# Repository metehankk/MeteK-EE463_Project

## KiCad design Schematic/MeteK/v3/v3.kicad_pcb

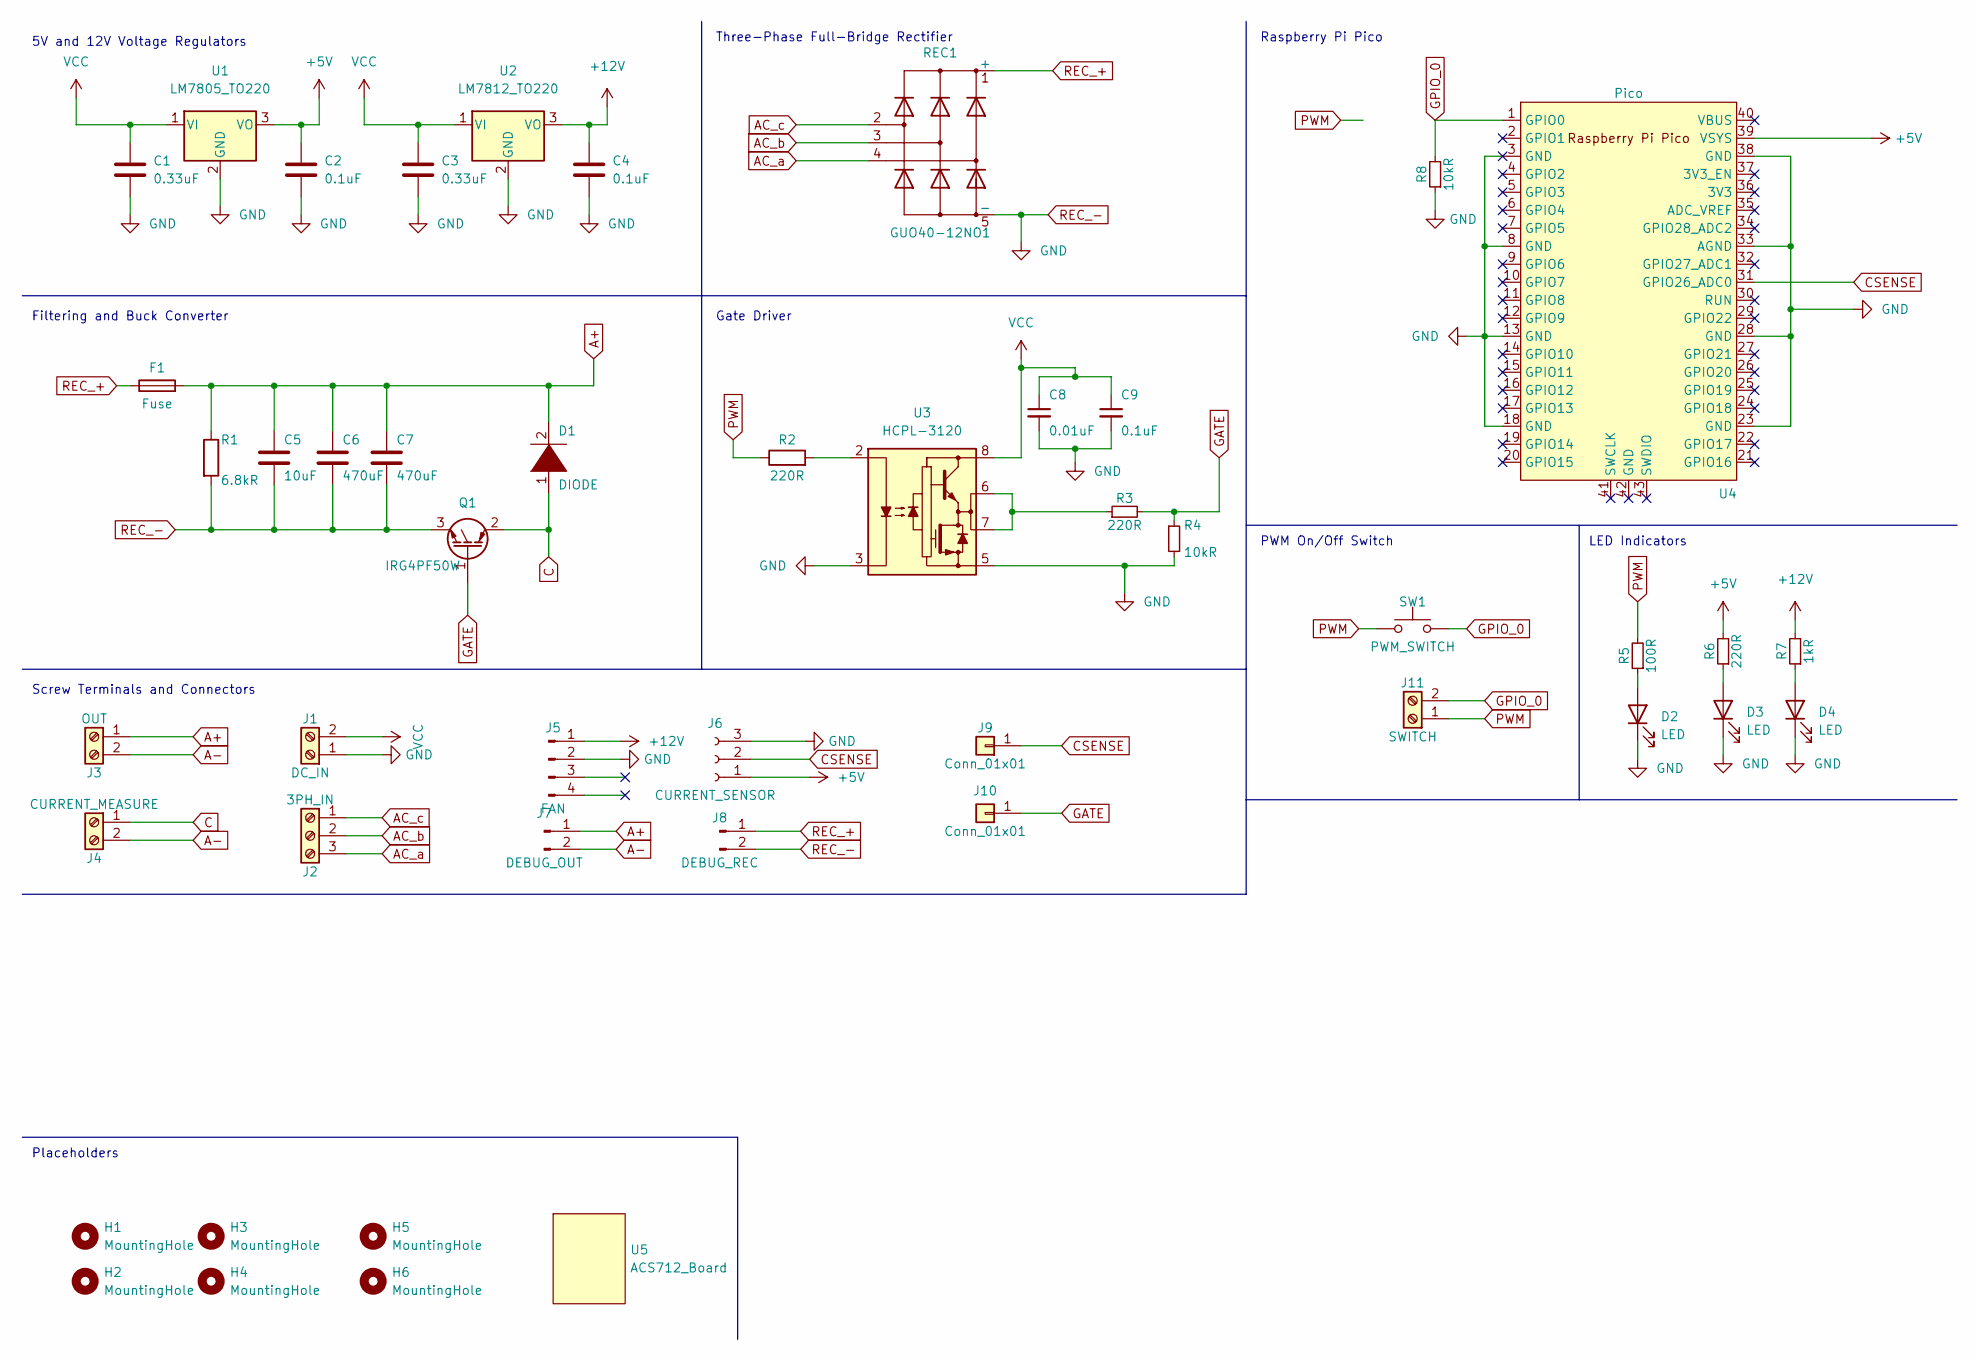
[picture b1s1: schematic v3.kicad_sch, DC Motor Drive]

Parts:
C1, C3: 0.33uF; C_1206_3216Metric_Pad1.33x1.80mm_HandSolder
C2, C4: 0.1uF; C_1206_3216Metric_Pad1.33x1.80mm_HandSolder
C5: 10uF; C_Rect_L29.0mm_W16.0mm_P27.50mm_MKT
C6, C7: 470uF; CP_Radial_D35.0mm_H50.0mm_P10.00mm_SnapIn
C8: 0.01uF; C_1206_3216Metric
C9: 0.1uF; C_1206_3216Metric
D1: DIODE; TO-220-2_Vertical
D2, D3, D4: LED; LED_D3.0mm
F1: Fuse; Fuseholder_Clip-5x20mm_Bel_FC-203-22_Lateral_P17.80x5.00mm_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
H1, H2, H3, H4: MountingHole; MountingHole_3.2mm_M3_Pad_Via
H5, H6: MountingHole; MountingHole_2.1mm
J1: DC_IN; TerminalBlock_Phoenix_MKDS-3-2-5.08_1x02_P5.08mm_Horizontal
J2: 3PH_IN; P7.62mm_ScrewTerminal_01x03
J3: OUT; P7.62mm_ScrewTerminal_01x02
J4: CURRENT_MEASURE; P7.62mm_ScrewTerminal_01x02
J5: FAN; PhoenixContact_MSTBVA_2,5_4-G-5,08_1x04_P5.08mm_Vertical
J6: CURRENT_SENSOR; PinSocket_1x03_P2.54mm_Vertical
J7: DEBUG_OUT; PinHeader_1x02_P2.54mm_Vertical
J8: DEBUG_REC; PinHeader_1x02_P2.54mm_Vertical
J9, J10: Conn_01x01; PinHeader_1x01_P2.54mm_Vertical
J11: SWITCH; TerminalBlock_Phoenix_MPT-0,5-2-2.54_1x02_P2.54mm_Horizontal
Q1: IRG4PF50W; TO-247-3_Vertical
R1: 6.8kR; R_Axial_Power_L50.0mm_W9.0mm_P55.88mm
R2, R3, R6: 220R; R_1206_3216Metric_Pad1.30x1.75mm_HandSolder
R4, R8: 10kR; R_1206_3216Metric_Pad1.30x1.75mm_HandSolder
R5: 100R; R_1206_3216Metric_Pad1.30x1.75mm_HandSolder
R7: 1kR; R_1206_3216Metric_Pad1.30x1.75mm_HandSolder
REC1: GUO40-12NO1; Diode_Bridge_IXYS_GUFP
SW1: PWM_SWITCH
U1: LM7805_TO220; TO-220-3_Vertical
U2: LM7812_TO220; TO-220-3_Vertical
U3: HCPL-3120; DIP-8_W7.62mm
U4: Pico; RPi_Pico_SMD_TH
U5: ACS712_Board; Current_sensor

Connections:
+5V: C2.1, J6.1, R6.2, U1.3 (VO), U4.39 (VSYS)
+12V: C4.1, J5.1, R7.2, U2.3 (VO)
A+: C5.1, C6.1, C7.1, D1.2 (A), F1.2, J3.1, J7.1, R1.1
A-: J3.2, J4.2, J7.2
AC_a: J2.3, REC1.4
AC_b: J2.2, REC1.3
AC_c: J2.1, REC1.2
C: D1.1 (K), J4.1, Q1.2 (C)
CSENSE: J6.2, J9.1, U4.31 (GPIO26_ADC0)
GATE: J10.1, Q1.1 (G), R3.2, R4.1
GPIO_0: J11.2, R8.2, SW1.2, U4.1 (GPIO0)
unnamed: D2.2 (A), R5.1
unnamed: D3.2 (A), R6.1
unnamed: D4.2 (A), R7.1
unnamed: R2.2, U3.2 (A)
unnamed: R3.1, U3.6 (VO), U3.7 (VO)
PWM: J11.1, R2.1, R5.2, SW1.1
REC_+: F1.1, J8.1, REC1.1 (+)
REC_-: C1.2, C2.2, C3.2, C4.2, C5.2, C6.2, C7.2, C8.2, C9.2, D2.1 (K), D3.1 (K), D4.1 (K), J1.1, J5.2, J6.3, J8.2, Q1.3 (E), R1.2, R4.2, R8.1, REC1.5 (-), U1.2 (GND), U2.2 (GND), U3.3 (C), U3.5 (VEE), U4.3 (GND), U4.8 (GND), U4.13 (GND), U4.18 (GND), U4.23 (GND), U4.28 (GND), U4.33 (AGND), U4.38 (GND)
VCC: C1.1, C3.1, C8.1, C9.1, J1.2, U1.1 (VI), U2.1 (VI), U3.8 (VCC)

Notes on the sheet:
LED Indicators
5V and 12V Voltage Regulators
Gate Driver
PWM On/Off Switch
Placeholders
Three-Phase Full-Bridge Rectifier
Raspberry Pi Pico
Filtering and Buck Converter
Screw Terminals and Connectors

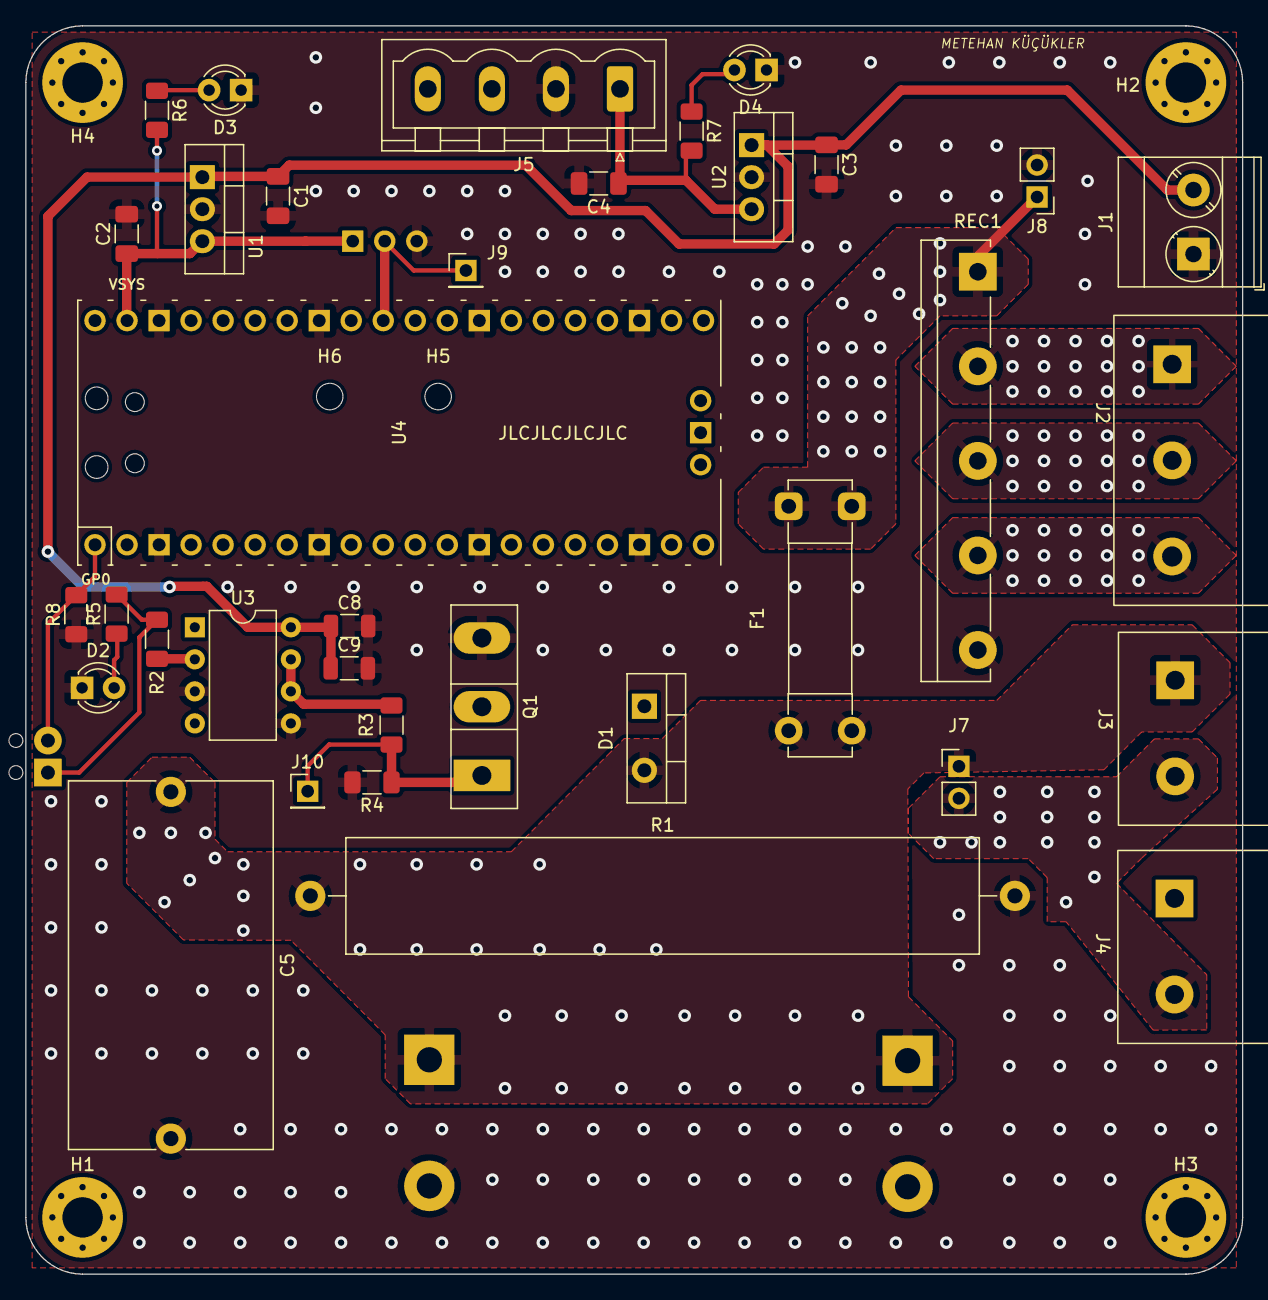
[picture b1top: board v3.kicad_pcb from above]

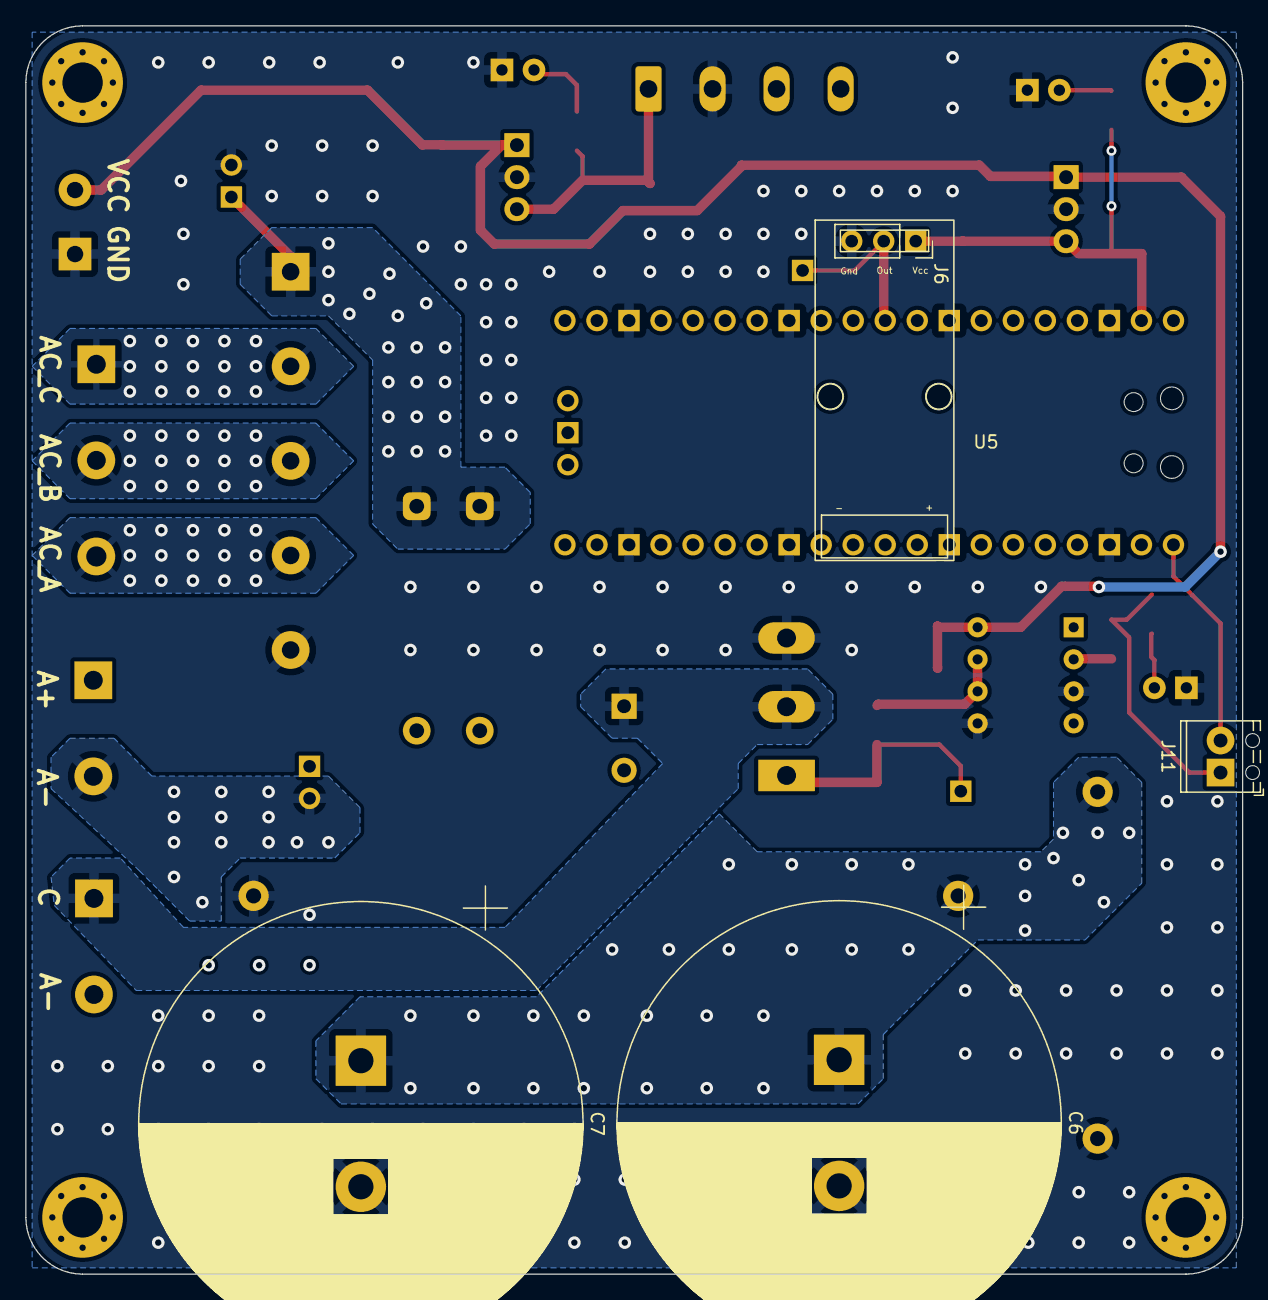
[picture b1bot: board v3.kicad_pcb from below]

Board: 2 copper layers, 96.5 x 99.0 mm, 46 parts (5 on the bottom side), 20 nets.

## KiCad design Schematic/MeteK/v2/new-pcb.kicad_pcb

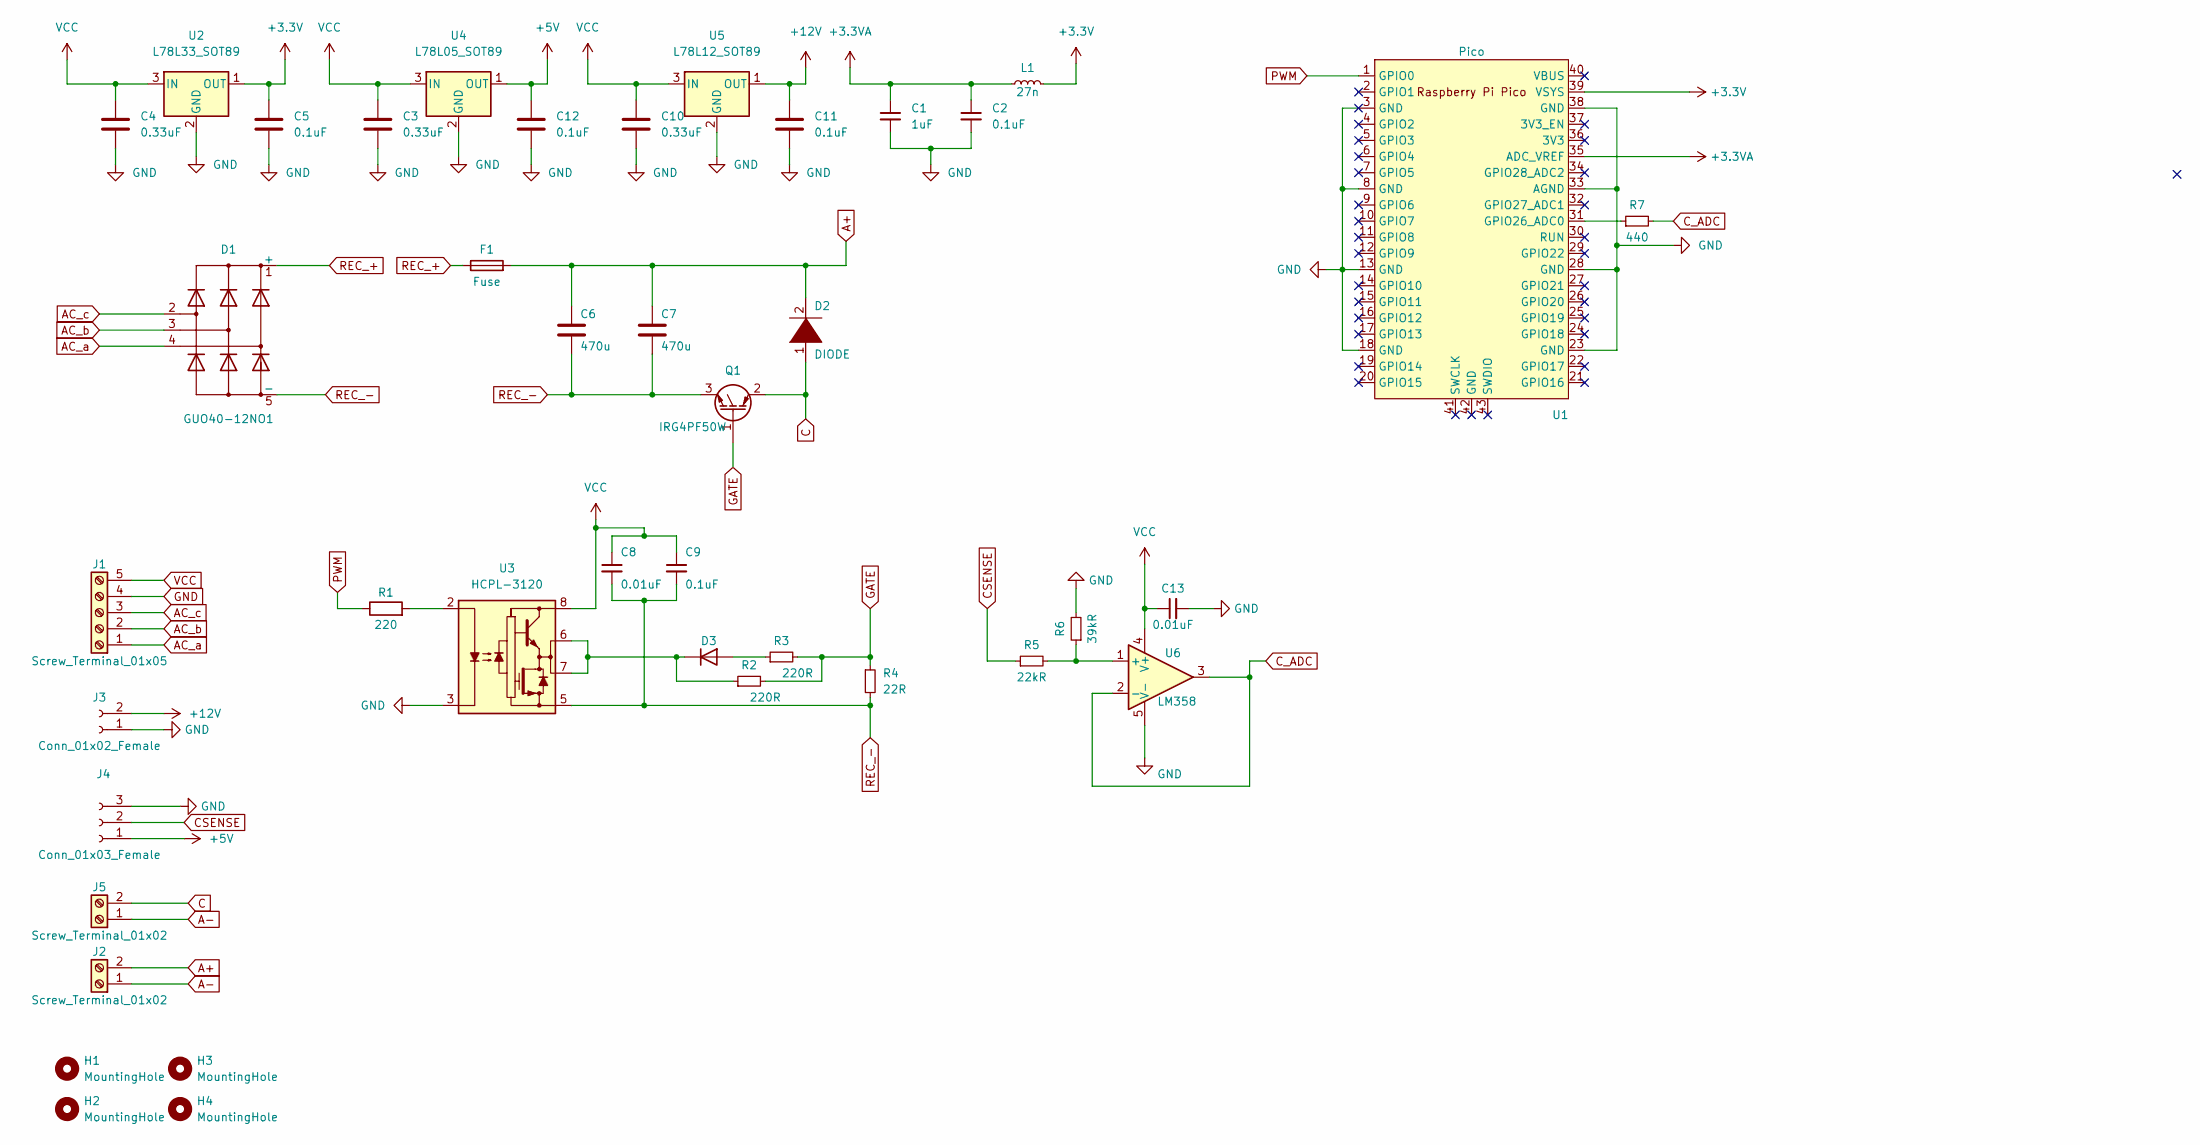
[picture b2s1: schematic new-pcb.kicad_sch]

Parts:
C1: 1uF; C_1206_3216Metric
C2, C5, C9, C11, C12: 0.1uF; C_1206_3216Metric
C3, C4, C10: 0.33uF; C_1206_3216Metric
C6, C7: 470u; CP_Radial_D35.0mm_P10.00mm_SnapIn
C8, C13: 0.01uF; C_1206_3216Metric
D1: GUO40-12NO1; Diode_Bridge_IXYS_GUFP
D2: DIODE; TO-220-2_Vertical
D3: 1N4148; D_SMB
F1: Fuse; Fuseholder_Clip-5x20mm_Bel_FC-203-22_Lateral_P17.80x5.00mm_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
H1, H2, H3, H4: MountingHole; MountingHole_3.2mm_M3_Pad
J1: Screw_Terminal_01x05; TerminalBlock_Phoenix_MKDS-3-5-5.08_1x05_P5.08mm_Horizontal
J2, J5: Screw_Terminal_01x02; TerminalBlock_Phoenix_MKDS-3-2-5.08_1x02_P5.08mm_Horizontal
J3: Conn_01x02_Female; PinHeader_1x02_P2.54mm_Vertical
J4: Conn_01x03_Female; PinSocket_1x03_P2.54mm_Vertical
L1: 27n; L_1206_3216Metric
Q1: IRG4PF50W; TO-247-3_Vertical
R1: 220; R_0603_1608Metric
R2, R3: 220R; R_0805_2012Metric
R4: 22R; R_0805_2012Metric
R5: 22kR; R_0805_2012Metric
R6: 39kR; R_0805_2012Metric
R7: 440; R_0805_2012Metric
U1: Pico; RPi_Pico_SMD_TH
U2: L78L33_SOT89; SOT-89-3
U3: HCPL-3120; DIP-8_W7.62mm
U4: L78L05_SOT89; SOT-89-3
U5: L78L12_SOT89; SOT-89-3
U6: LM358; DIP-8_W7.62mm

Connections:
+3.3V: C5.1, L1.2, U1.39 (VSYS), U2.1 (OUT)
+3.3VA: C1.1, C2.1, L1.1, U1.35 (ADC_VREF)
+5V: C12.1, J4.1, U4.1 (OUT)
+12V: C11.1, J3.2, U5.1 (OUT)
A+: C6.1, C7.1, D2.2 (A), F1.2, J2.2
A-: J2.1, J5.1
AC_a: D1.4, J1.1
AC_b: D1.3, J1.2
AC_c: D1.2, J1.3
C: D2.1 (K), J5.2, Q1.2 (C)
CSENSE: J4.2, R5.1
C_ADC: R7.2, U6.2 (-), U6.3
GATE: Q1.1 (G), R2.2, R3.2, R4.1
GND: C1.2, C2.2, C3.2, C4.2, C5.2, C10.2, C11.2, C12.2, C13.2, J1.4, J3.1, J4.3, R6.2, U1.3 (GND), U1.8 (GND), U1.13 (GND), U1.18 (GND), U1.23 (GND), U1.28 (GND), U1.33 (AGND), U1.38 (GND), U2.2 (GND), U3.3 (C), U4.2 (GND), U5.2 (GND), U6.5 (V-)
unnamed: D3.1 (K), R2.1, U3.6 (VO), U3.7 (VO)
unnamed: D3.2 (A), R3.1
unnamed: R1.2, U3.2 (A)
unnamed: R5.2, R6.1, U6.1 (+)
unnamed: R7.1, U1.31 (GPIO26_ADC0)
PWM: R1.1, U1.1 (GPIO0)
REC_+: D1.1 (+), F1.1
REC_-: C6.2, C7.2, C8.2, C9.2, D1.5 (-), Q1.3 (E), R4.2, U3.5 (VEE)
VCC: C3.1, C4.1, C8.1, C9.1, C10.1, C13.1, J1.5, U2.3 (IN), U3.8 (VCC), U4.3 (IN), U5.3 (IN), U6.4 (V+)

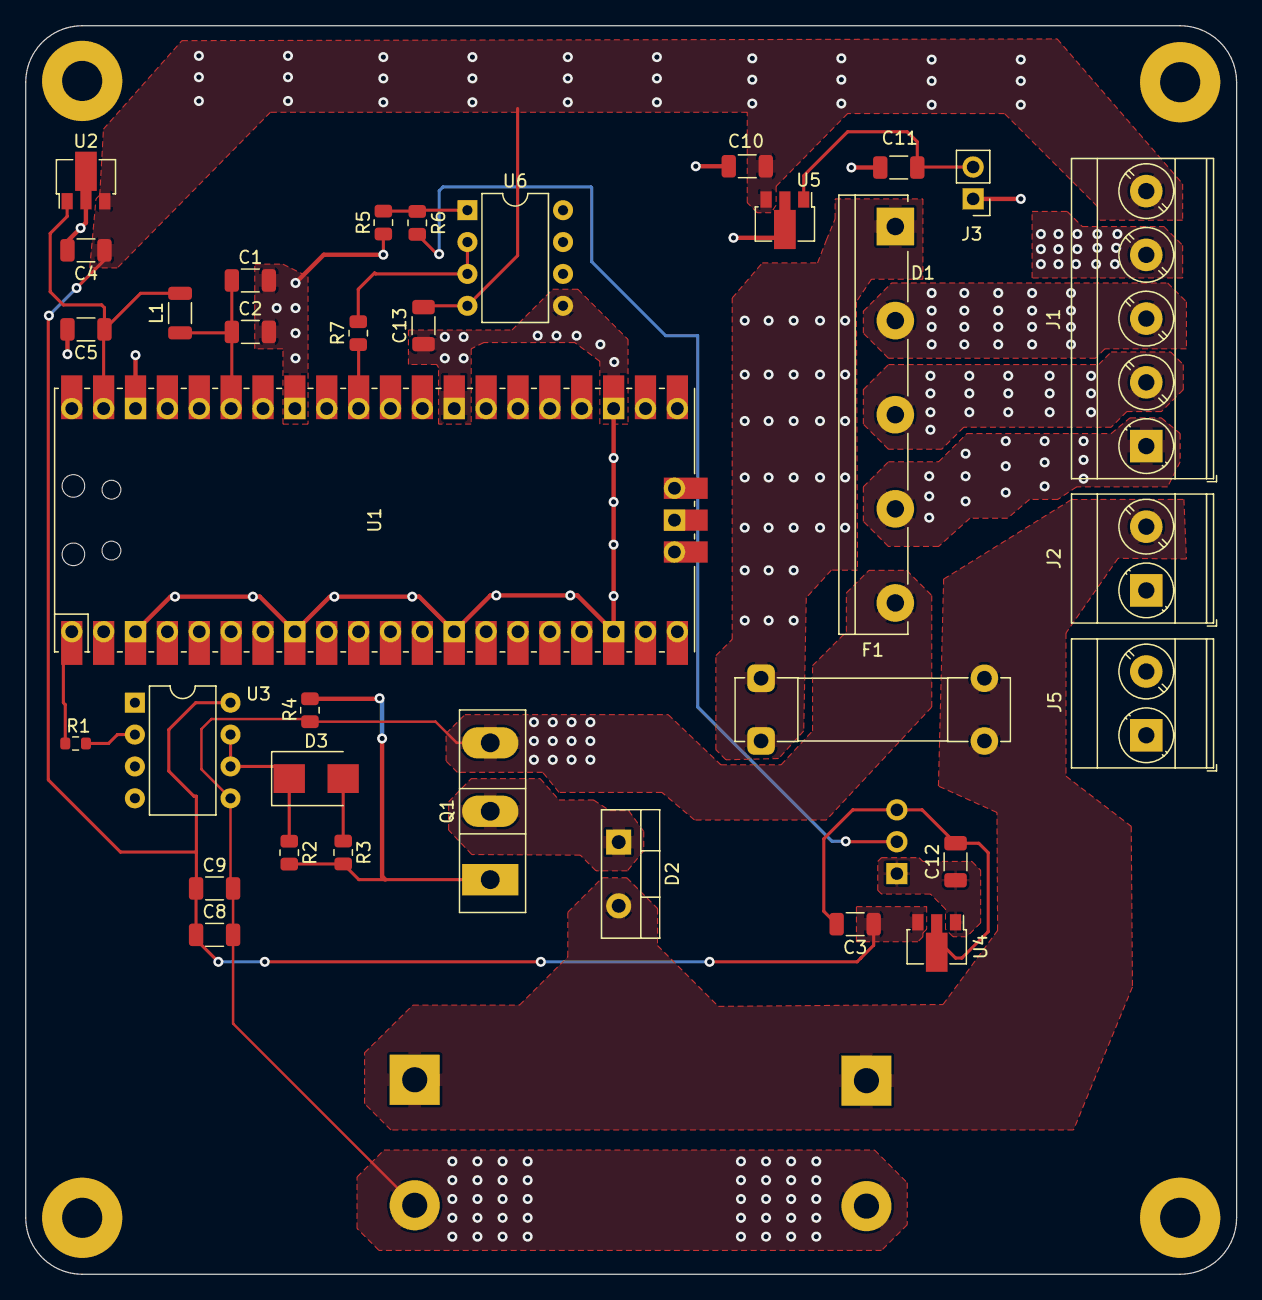
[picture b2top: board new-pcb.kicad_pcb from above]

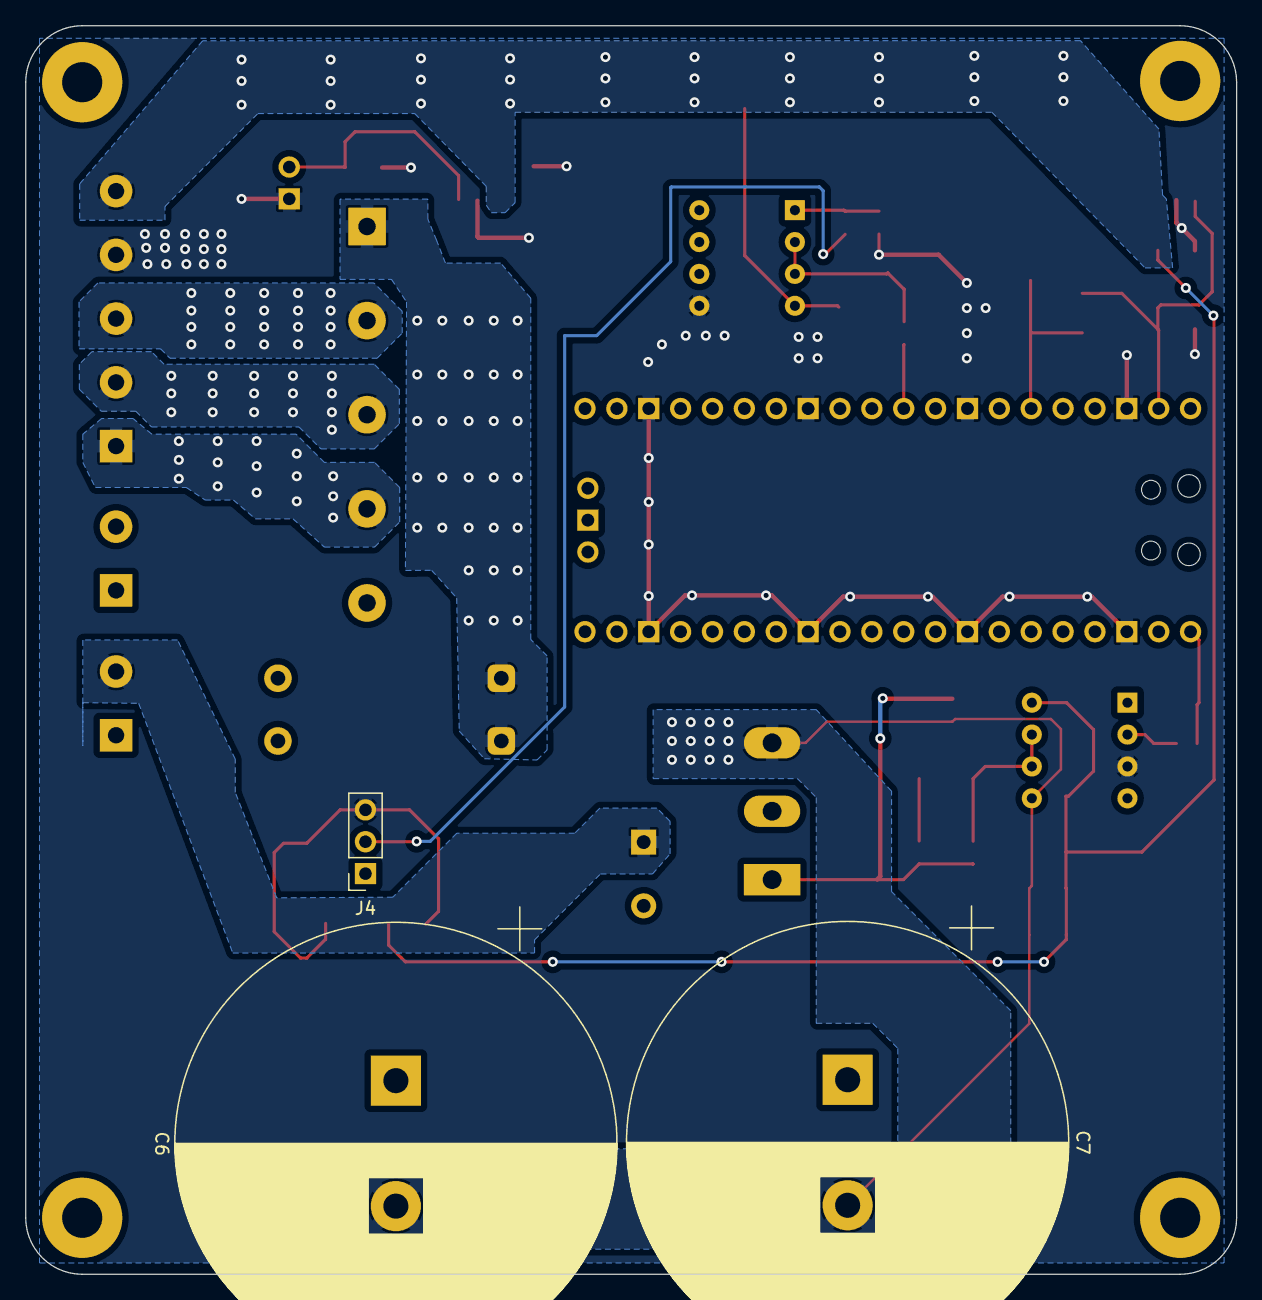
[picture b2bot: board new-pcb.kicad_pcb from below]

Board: 2 copper layers, 96.5 x 99.5 mm, 41 parts (3 on the bottom side), 23 nets.

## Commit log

2022-12-02 Repo initialization
2022-12-10 Simulink simulations and simulation report are added.
2022-12-12 Frequency and Duty Cycle control with potentiometer added.
2022-12-12 Presentation documents are added.
2022-12-12 Typo
2022-12-12 Presentation pdf.
2022-12-12 Schottky diode changed to fast diode.
2022-12-12 Closed-loop armature current control added. Simulink schematic is cleaned up. Current sensing w/opamp and opto-coupler test in LTspice are done.
2022-12-14 Components are selected. LTspice implementation is added with specific components.
2022-12-19 Gate driver fixes. Initial KiCad schematic and PCB design trials. Updates on components.
2022-12-22 further tests on schematic and pcb layout.
2022-12-28 Schematic and PCB layout are finalized.
2023-01-02 Initial case design are created.
2023-01-05 Case design is finalized.
2023-01-05 File names are corrected.
2023-01-24 Final commit before last submission.
